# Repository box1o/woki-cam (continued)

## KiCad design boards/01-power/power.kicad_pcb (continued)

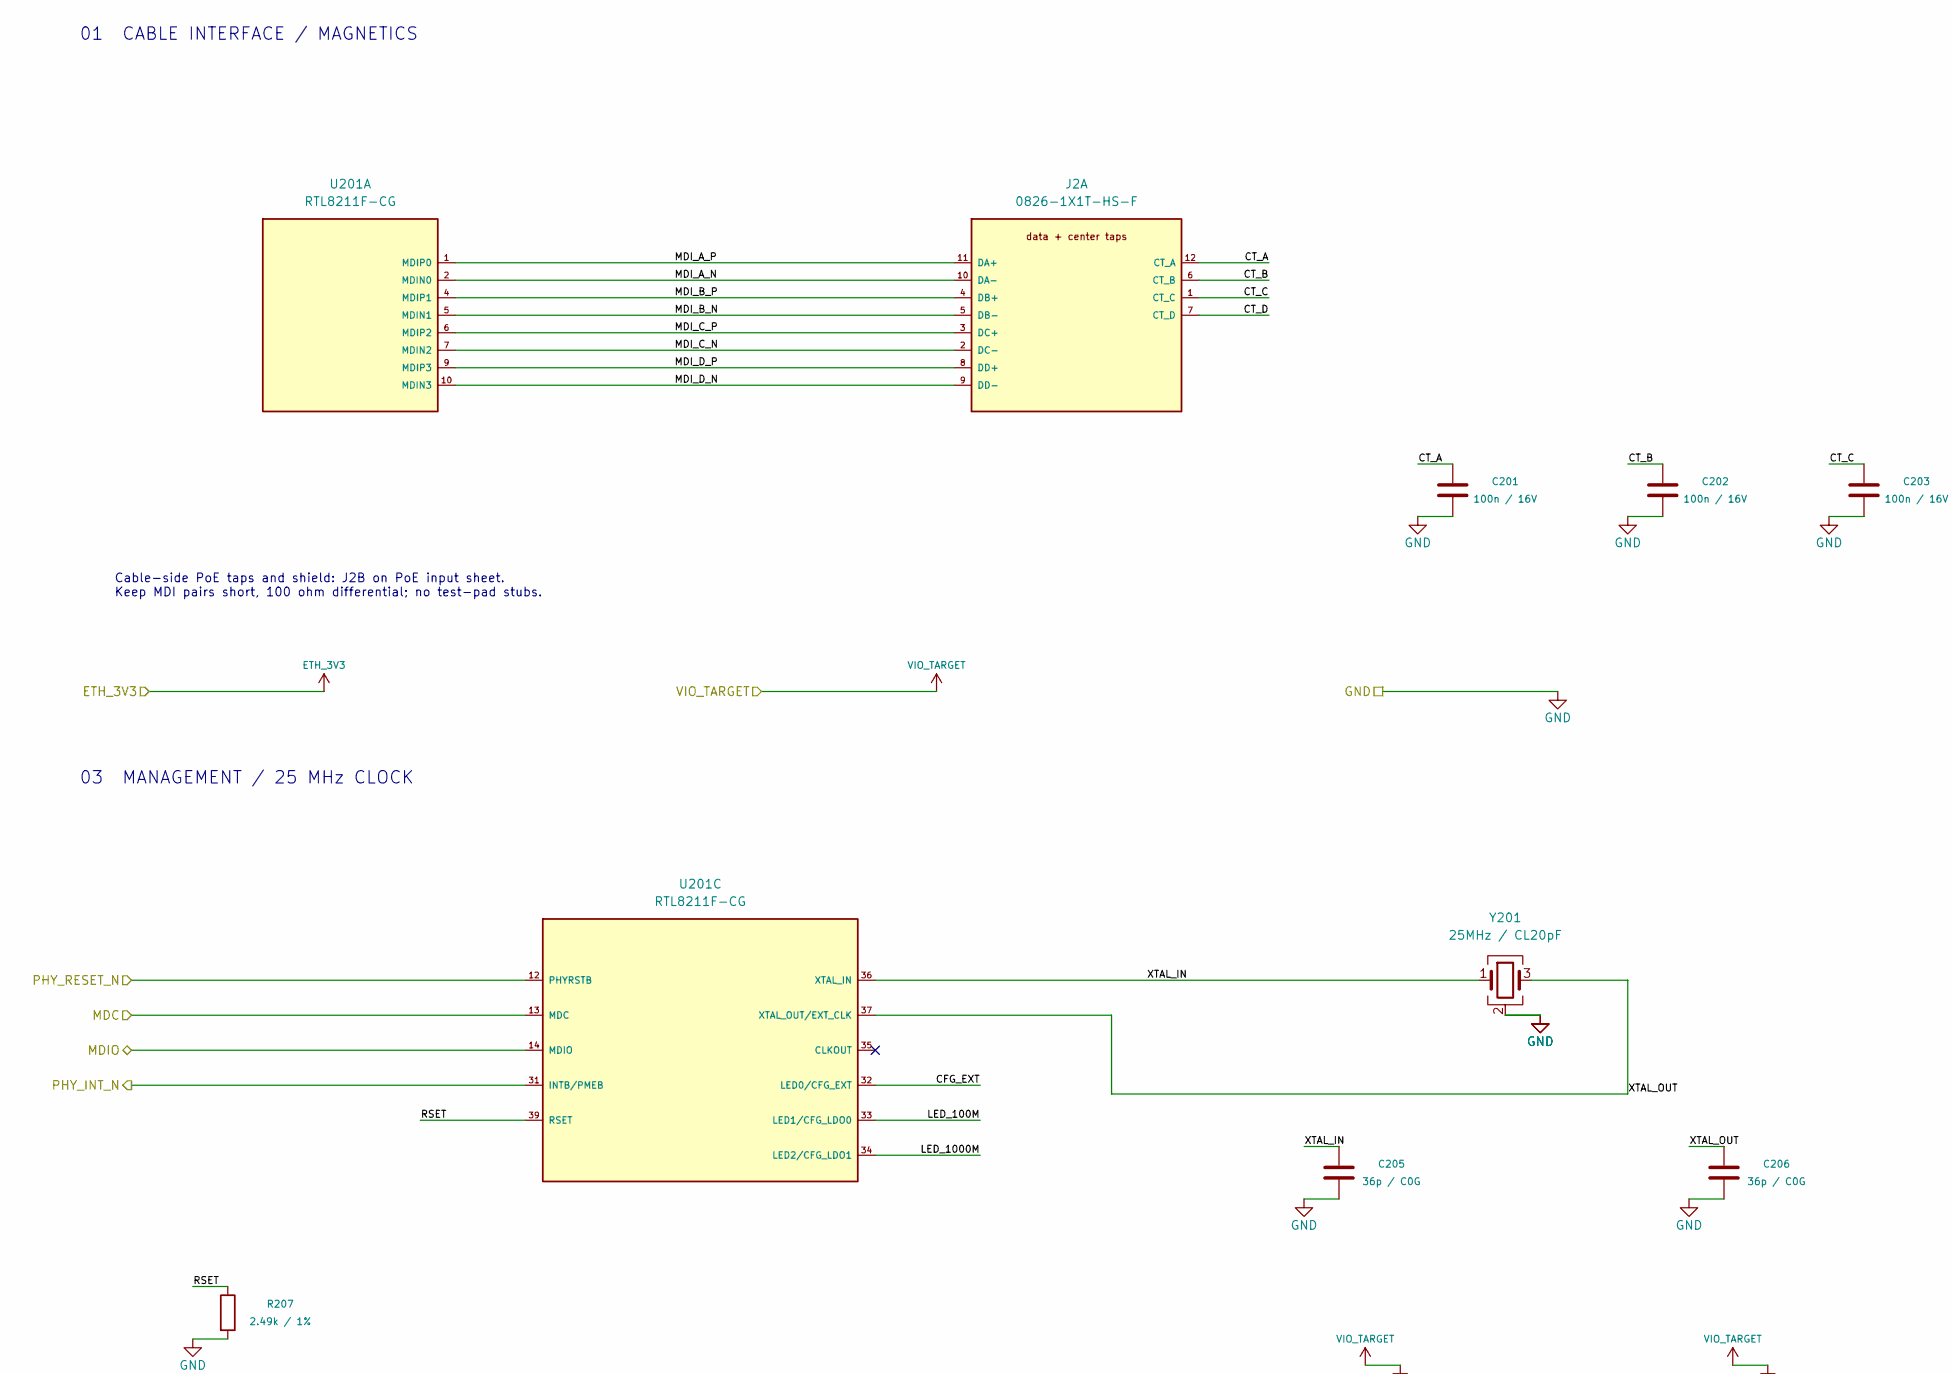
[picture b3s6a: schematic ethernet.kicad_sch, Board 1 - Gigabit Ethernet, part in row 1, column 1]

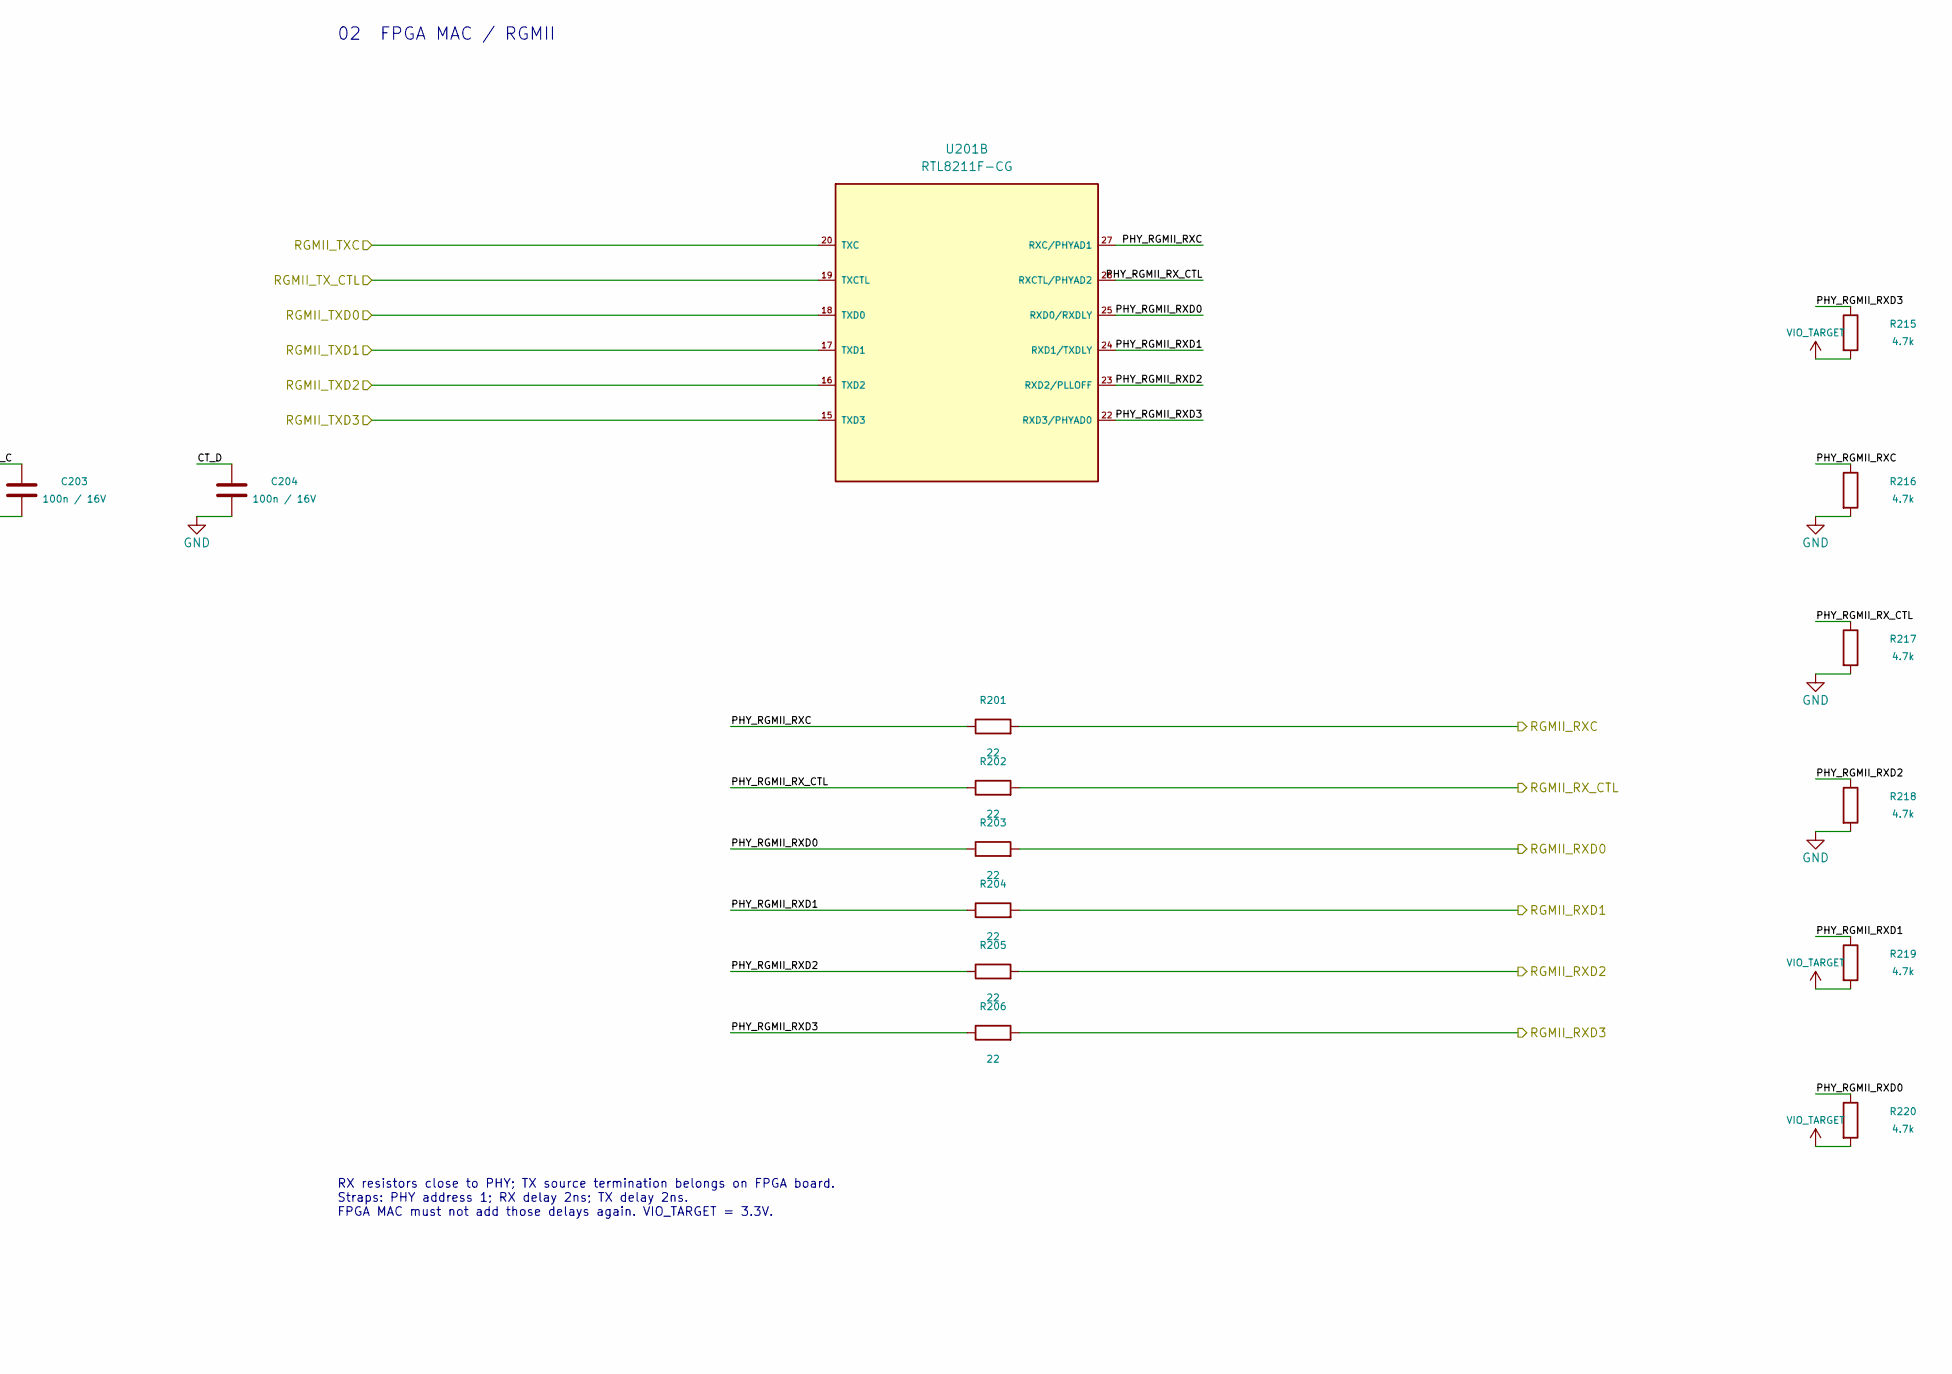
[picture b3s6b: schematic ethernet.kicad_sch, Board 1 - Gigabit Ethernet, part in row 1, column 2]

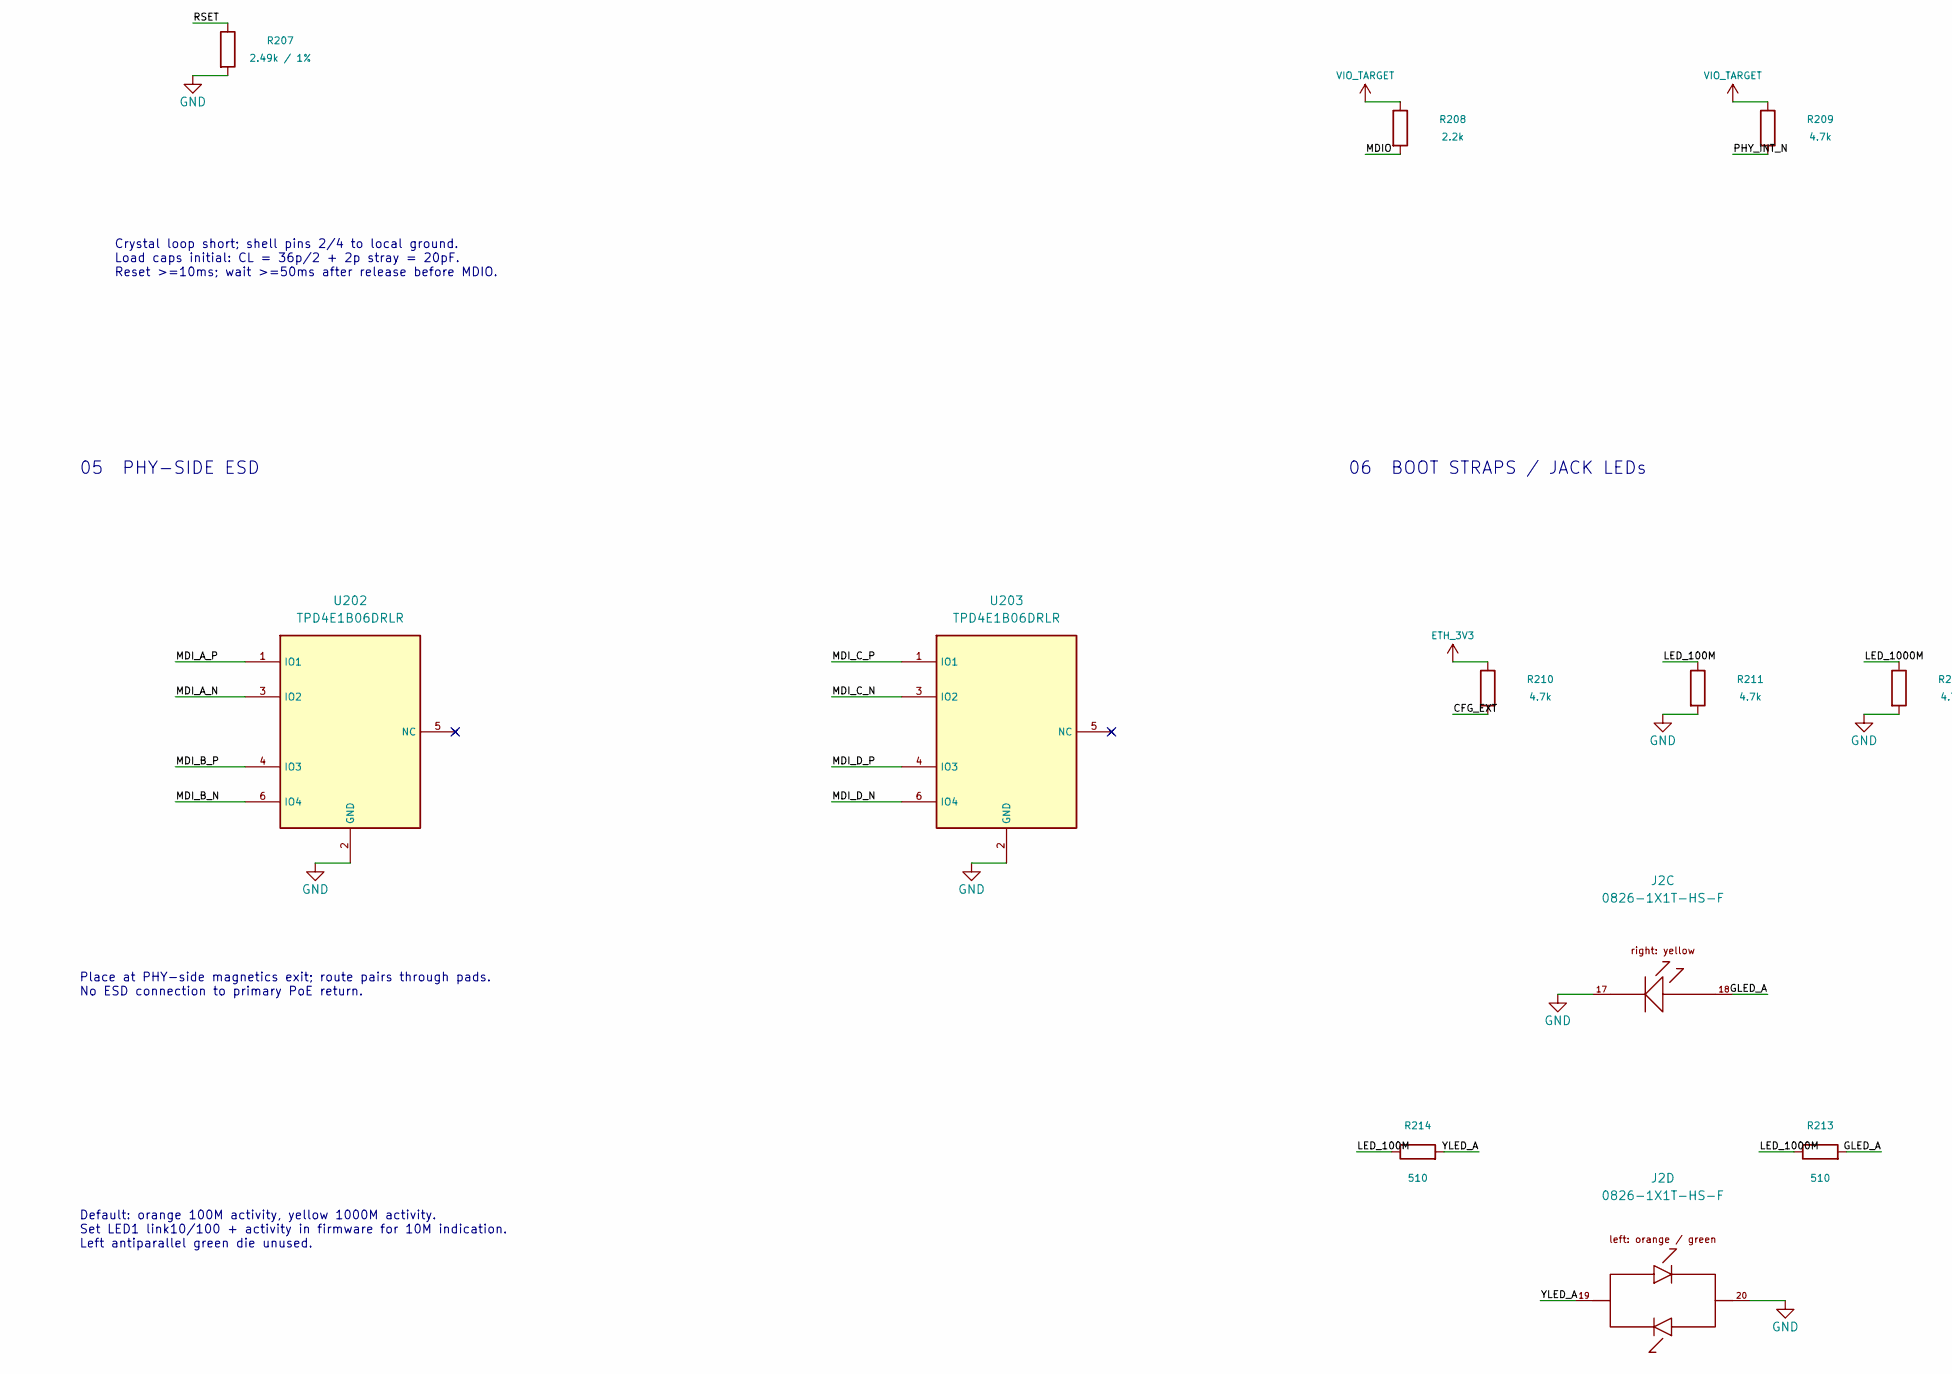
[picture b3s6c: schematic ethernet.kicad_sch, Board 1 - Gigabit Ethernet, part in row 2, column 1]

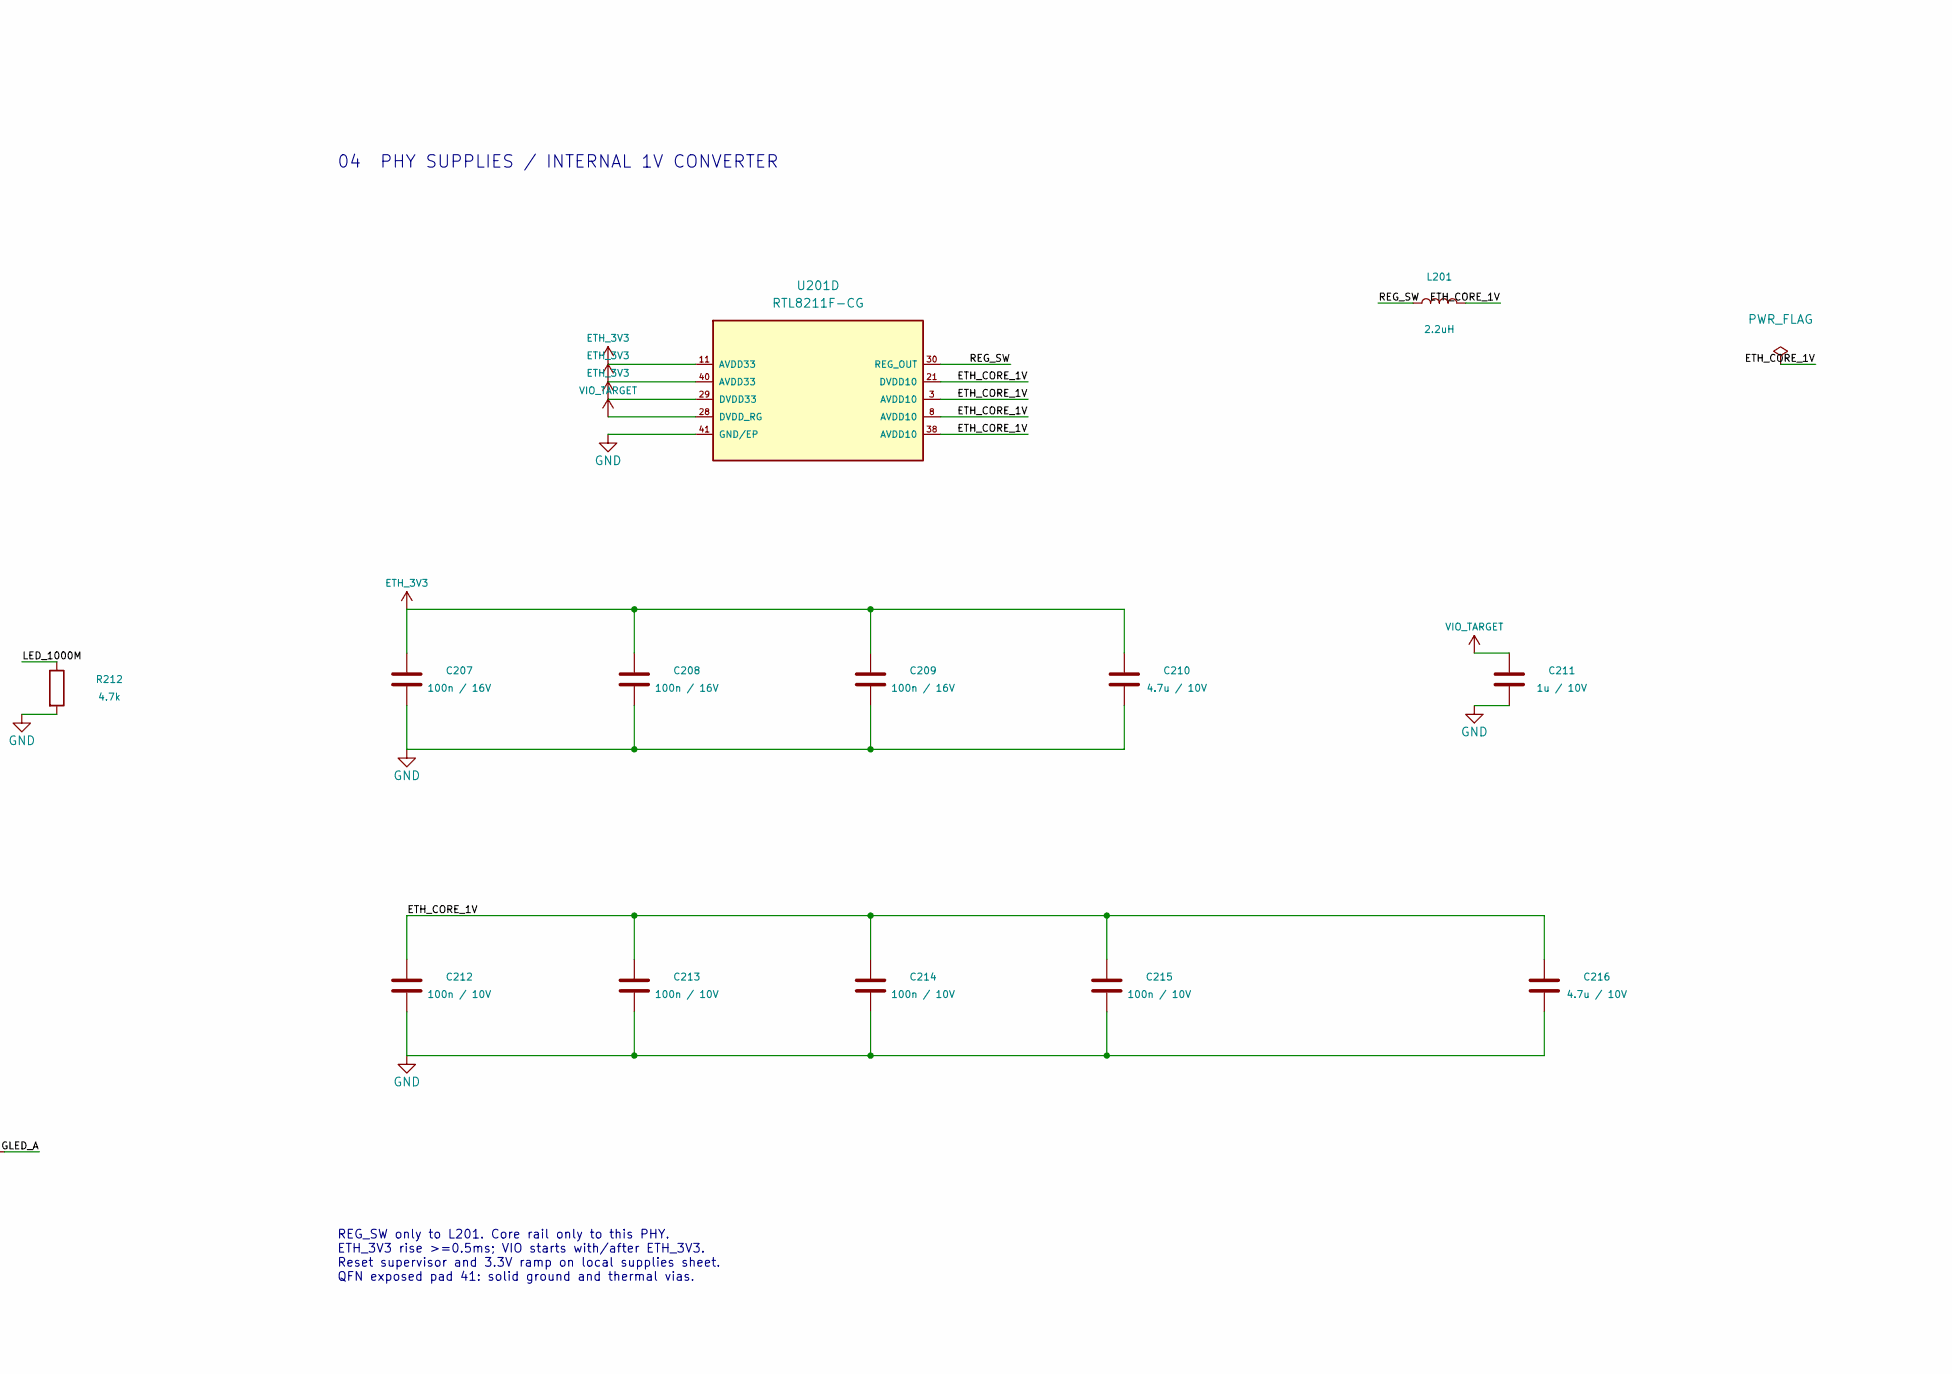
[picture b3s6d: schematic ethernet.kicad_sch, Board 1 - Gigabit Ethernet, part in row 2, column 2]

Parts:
C201, C202, C203, C204, C207, C208, C209: 100n / 16V; C_0603_1608Metric
C205, C206: 36p / C0G; C_0603_1608Metric
C210, C216: 4.7u / 10V; C_0603_1608Metric
C211: 1u / 10V; C_0603_1608Metric
C212, C213, C214, C215: 100n / 10V; C_0603_1608Metric
J2: 0826-1X1T-HS-F; 0826-1x1t-hs-f
L201: 2.2uH; lps4018; MPN LPS4018-222MR
R201, R202, R203, R204, R205, R206: 22; R_0603_1608Metric
R207: 2.49k / 1%; R_0603_1608Metric
R208: 2.2k; R_0603_1608Metric
R209, R210, R211, R212, R215, R216, R217, R218, R219, R220: 4.7k; R_0603_1608Metric
R213, R214: 510; R_0603_1608Metric
U201: RTL8211F-CG; rtl8211f-cg
U202, U203: TPD4E1B06DRLR; SOT-563
Y201: 25MHz / CL20pF; Crystal_SMD_3225-4Pin_3.2x2.5mm; MPN X322525MSB4SI

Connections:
/Gigabit Ethernet/CFG_EXT: R210.2, U201.32 (LED0/CFG_EXT)
/Gigabit Ethernet/CT_A: C201.1, J2.12 (CT_A)
/Gigabit Ethernet/CT_B: C202.1, J2.6 (CT_B)
/Gigabit Ethernet/CT_C: C203.1, J2.1 (CT_C)
/Gigabit Ethernet/CT_D: C204.1, J2.7 (CT_D)
/Gigabit Ethernet/ETH_CORE_1V: C212.1, C213.1, C214.1, C215.1, C216.1, L201.2, U201.3 (AVDD10), U201.8 (AVDD10), U201.21 (DVDD10), U201.38 (AVDD10)
/Gigabit Ethernet/GLED_A: J2.18, R213.2
/Gigabit Ethernet/LED_100M: R211.1, R214.1, U201.33 (LED1/CFG_LDO0)
/Gigabit Ethernet/LED_1000M: R212.1, R213.1, U201.34 (LED2/CFG_LDO1)
/Gigabit Ethernet/MDI_A_N: J2.10 (DA-), U201.2 (MDIN0), U202.3 (IO2)
/Gigabit Ethernet/MDI_A_P: J2.11 (DA+), U201.1 (MDIP0), U202.1 (IO1)
/Gigabit Ethernet/MDI_B_N: J2.5 (DB-), U201.5 (MDIN1), U202.6 (IO4)
/Gigabit Ethernet/MDI_B_P: J2.4 (DB+), U201.4 (MDIP1), U202.4 (IO3)
/Gigabit Ethernet/MDI_C_N: J2.2 (DC-), U201.7 (MDIN2), U203.3 (IO2)
/Gigabit Ethernet/MDI_C_P: J2.3 (DC+), U201.6 (MDIP2), U203.1 (IO1)
/Gigabit Ethernet/MDI_D_N: J2.9 (DD-), U201.10 (MDIN3), U203.6 (IO4)
/Gigabit Ethernet/MDI_D_P: J2.8 (DD+), U201.9 (MDIP3), U203.4 (IO3)
/Gigabit Ethernet/PHY_RGMII_RXC: R201.1, R216.1, U201.27 (RXC/PHYAD1)
/Gigabit Ethernet/PHY_RGMII_RXD0: R203.1, R220.1, U201.25 (RXD0/RXDLY)
/Gigabit Ethernet/PHY_RGMII_RXD1: R204.1, R219.1, U201.24 (RXD1/TXDLY)
/Gigabit Ethernet/PHY_RGMII_RXD2: R205.1, R218.1, U201.23 (RXD2/PLLOFF)
/Gigabit Ethernet/PHY_RGMII_RXD3: R206.1, R215.1, U201.22 (RXD3/PHYAD0)
/Gigabit Ethernet/PHY_RGMII_RX_CTL: R202.1, R217.1, U201.26 (RXCTL/PHYAD2)
/Gigabit Ethernet/REG_SW: L201.1, U201.30 (REG_OUT)
/Gigabit Ethernet/RSET: R207.1, U201.39 (RSET)
/Gigabit Ethernet/XTAL_IN: C205.1, U201.36 (XTAL_IN), Y201.1
/Gigabit Ethernet/XTAL_OUT: C206.1, U201.37 (XTAL_OUT/EXT_CLK), Y201.3
/Gigabit Ethernet/YLED_A: J2.19, R214.2
/MDC: U201.13 (MDC); also elsewhere on the board
/MDIO: R208.2, U201.14 (MDIO); also elsewhere on the board
/PHY_INT_N: R209.2, U201.31 (INTB/PMEB); also elsewhere on the board
/PHY_RESET_N: U201.12 (PHYRSTB); also elsewhere on the board
/RGMII_RXC: R201.2; also elsewhere on the board
/RGMII_RXD0: R203.2; also elsewhere on the board
/RGMII_RXD1: R204.2; also elsewhere on the board
/RGMII_RXD2: R205.2; also elsewhere on the board
/RGMII_RXD3: R206.2; also elsewhere on the board
/RGMII_RX_CTL: R202.2; also elsewhere on the board
/RGMII_TXC: U201.20 (TXC); also elsewhere on the board
/RGMII_TXD0: U201.18 (TXD0); also elsewhere on the board
/RGMII_TXD1: U201.17 (TXD1); also elsewhere on the board
/RGMII_TXD2: U201.16 (TXD2); also elsewhere on the board
/RGMII_TXD3: U201.15 (TXD3); also elsewhere on the board
/RGMII_TX_CTL: U201.19 (TXCTL); also elsewhere on the board
ETH_3V3: C207.1, C208.1, C209.1, C210.1, R210.1, U201.11 (AVDD33), U201.29 (DVDD33), U201.40 (AVDD33); also elsewhere on the board
VIO_TARGET: C211.1, R208.1, R209.1, R215.2, R219.2, R220.2, U201.28 (DVDD_RG); also elsewhere on the board

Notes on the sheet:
05 PHY-SIDE ESD
RX resistors close to PHY; TX source termination belongs on FPGA board. Straps: PHY address 1; RX delay 2ns; TX delay 2ns. FPGA MAC must not add those delays again. VIO_TARGET = 3.3V.
02 FPGA MAC / RGMII
Crystal loop short; shell pins 2/4 to local ground. Load caps initial: CL = 36p/2 + 2p stray = 20pF. Reset >=10ms; wait >=50ms after release before MDIO.
Cable-side PoE taps and shield: J2B on PoE input sheet. Keep MDI pairs short, 100 ohm differential; no test-pad stubs.
03 MANAGEMENT / 25 MHz CLOCK
01 CABLE INTERFACE / MAGNETICS
Default: orange 100M activity, yellow 1000M activity. Set LED1 link10/100 + activity in firmware for 10M indication. Left antiparallel green die unused.
Place at PHY-side magnetics exit; route pairs through pads. No ESD connection to primary PoE return.
06 BOOT STRAPS / JACK LEDs
04 PHY SUPPLIES / INTERNAL 1V CONVERTER
REG_SW only to L201. Core rail only to this PHY. ETH_3V3 rise >=0.5ms; VIO starts with/after ETH_3V3. Reset supervisor and 3.3V ramp on local supplies sheet. QFN exposed pad 41: solid ground and thermal vias.

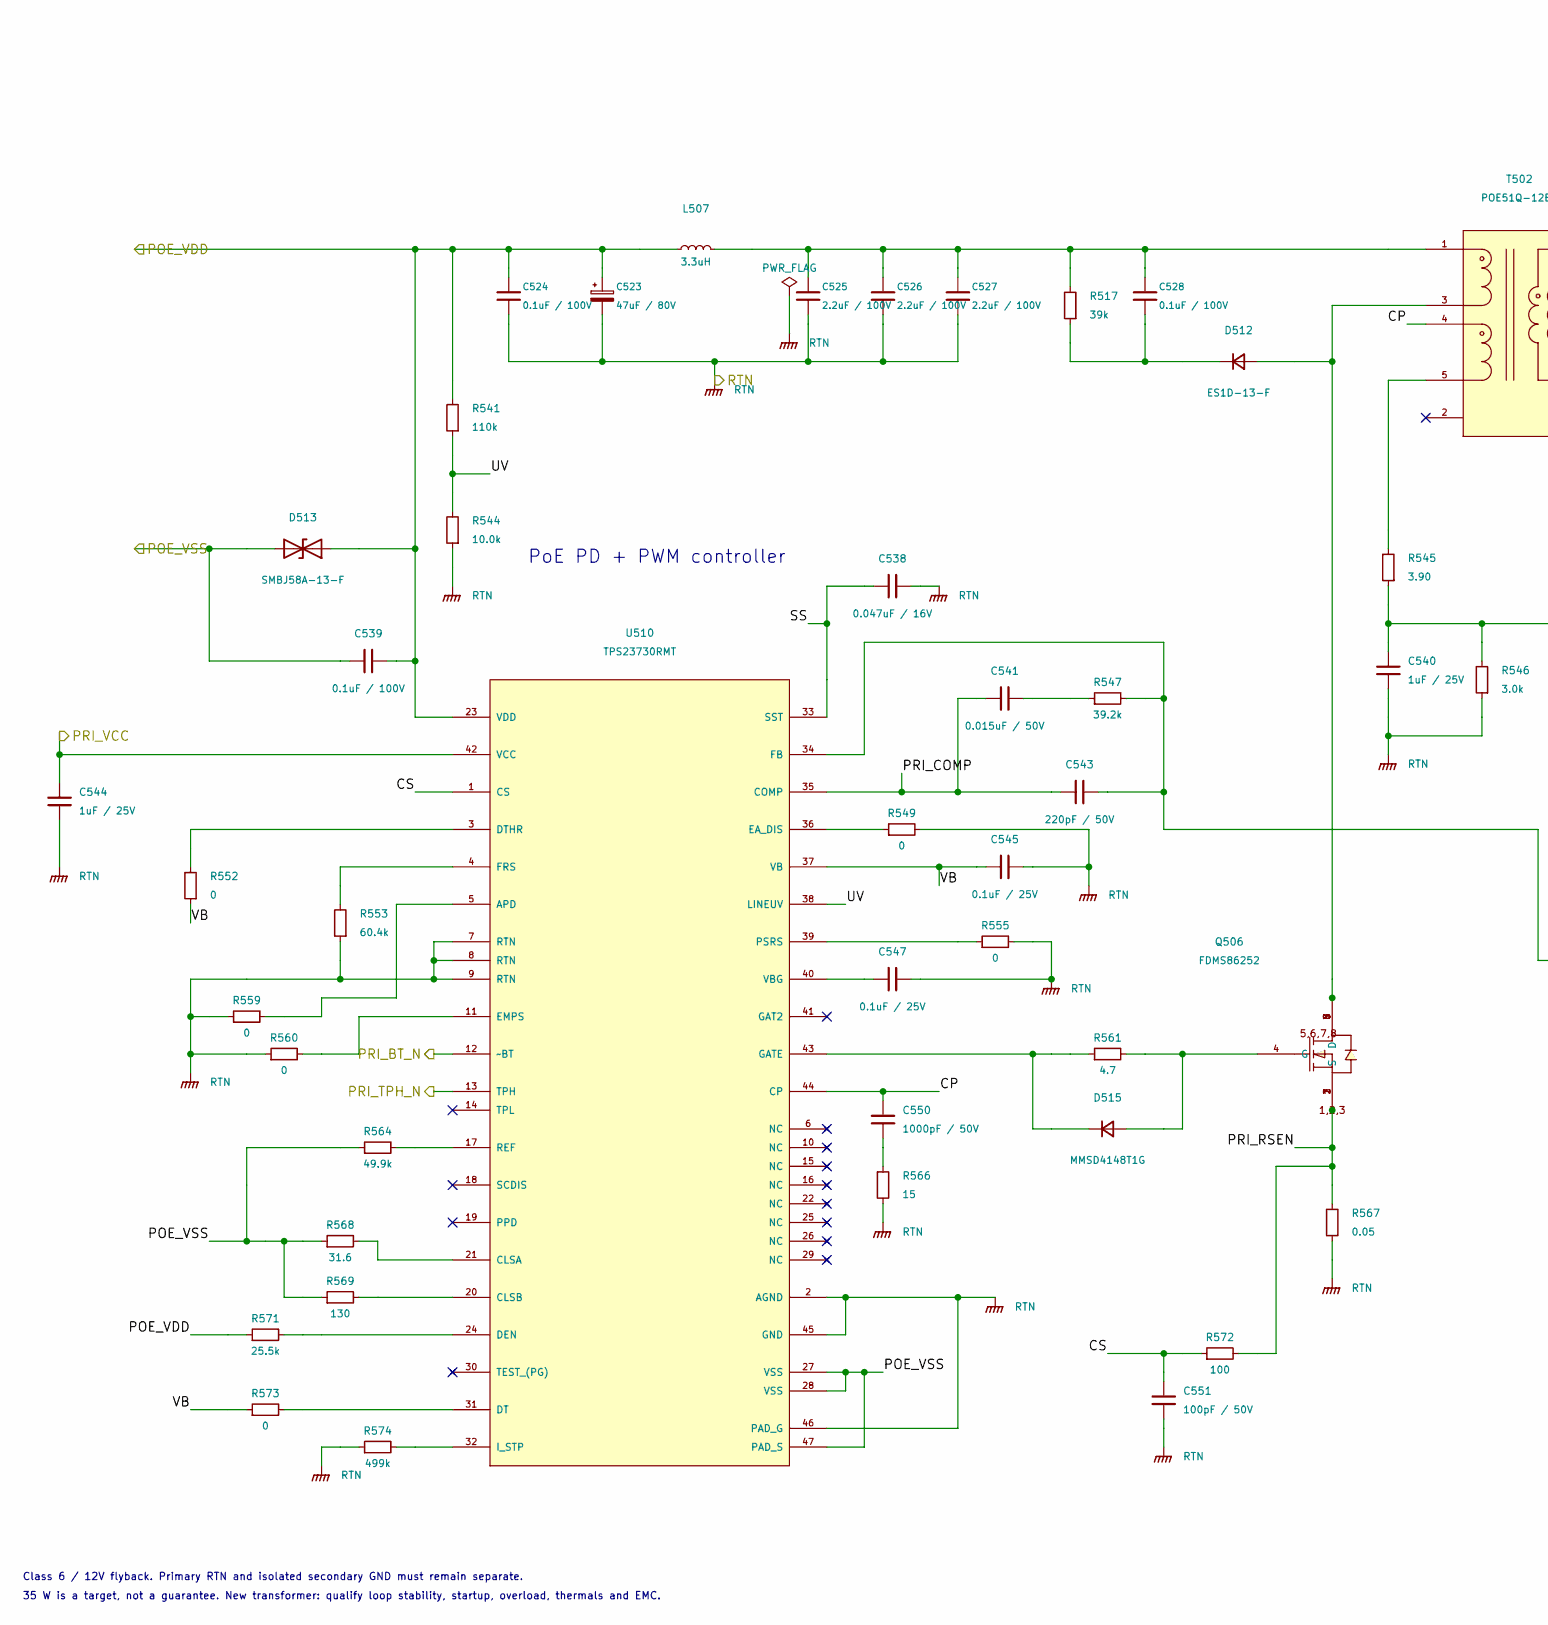
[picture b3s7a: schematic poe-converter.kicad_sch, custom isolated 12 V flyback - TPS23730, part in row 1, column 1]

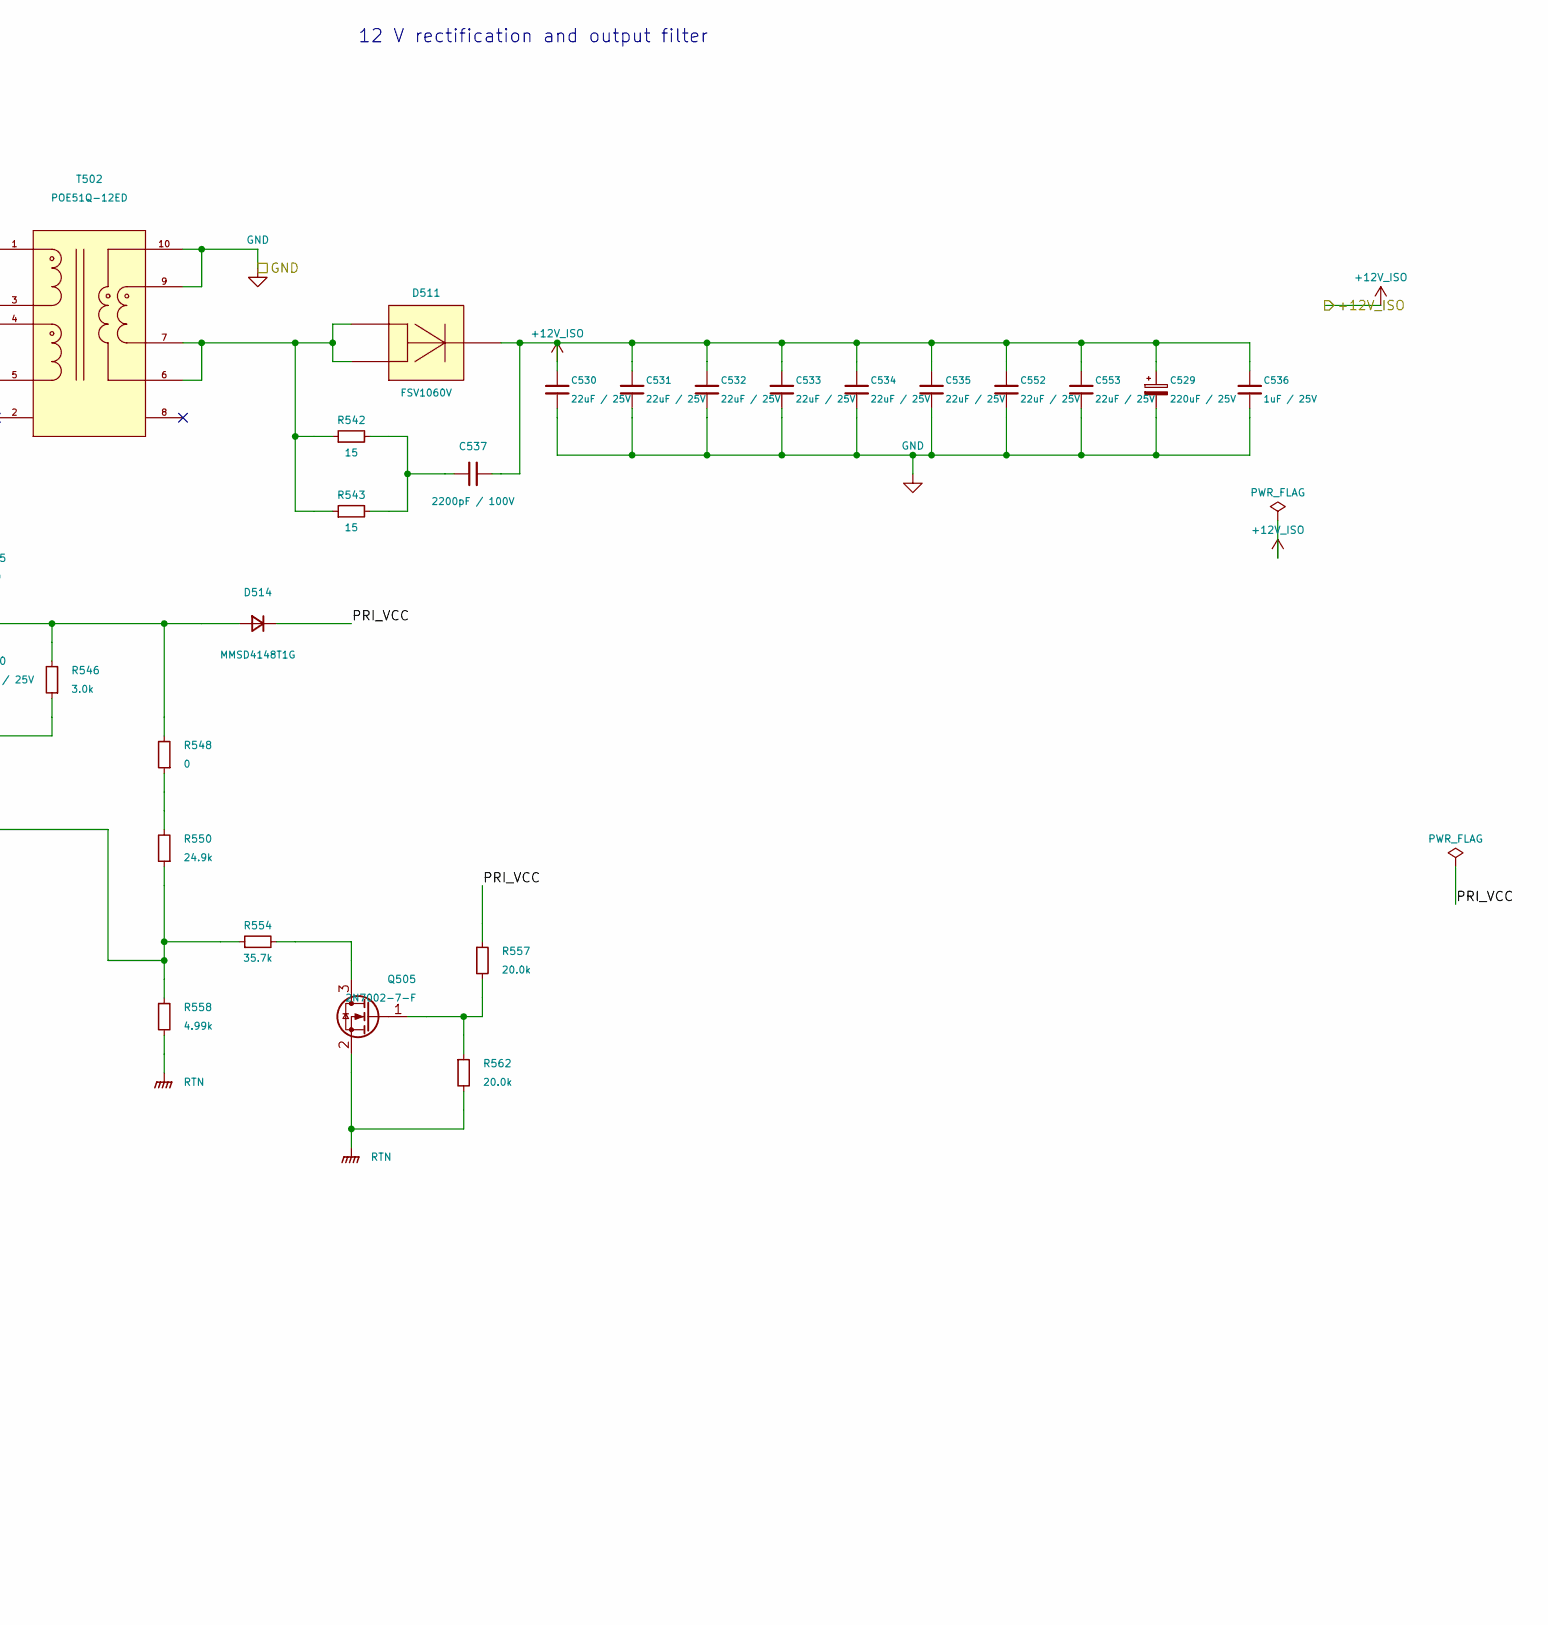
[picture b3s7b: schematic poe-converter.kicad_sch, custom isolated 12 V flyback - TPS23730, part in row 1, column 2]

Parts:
C523: 47uF / 80V; panasonic_fk_g_10x10.2
C524, C528, C539: 0.1uF / 100V; C_0805_2012Metric
C525, C526, C527: 2.2uF / 100V; C_1210_3225Metric
C529: 220uF / 25V; panasonic_fk_f_8x10.2
C530, C531, C532, C533, C534, C535, C552, C553: 22uF / 25V; C_1210_3225Metric
C536, C540, C544: 1uF / 25V; C_0603_1608Metric
C537: 2200pF / 100V; C_0603_1608Metric
C538: 0.047uF / 16V; C_0603_1608Metric
C541: 0.015uF / 50V; C_0603_1608Metric
C543: 220pF / 50V; C_0603_1608Metric
C545, C547: 0.1uF / 25V; C_0603_1608Metric
C550: 1000pF / 50V; C_0603_1608Metric
C551: 100pF / 50V; C_0603_1608Metric
D511: FSV1060V; TO-277A
D512: ES1D-13-F; D_SMA
D513: SMBJ58A-13-F; D_SMB
D514, D515: MMSD4148T1G; D_SOD-123
L507: 3.3uH; lps4018-332mlb
Q505: 2N7002-7-F; SOT-23
Q506: FDMS86252; fdms86252
R517: 39k; R_1206_3216Metric
R541: 110k; R_0603_1608Metric
R542, R543: 15; R_2512_6332Metric
R544: 10.0k; R_0603_1608Metric
R545: 3.90; R_0805_2012Metric
R546: 3.0k; R_1206_3216Metric
R547: 39.2k; R_0603_1608Metric
R548, R549, R552, R555, R559, R560, R573: 0; R_0603_1608Metric
R550: 24.9k; R_0603_1608Metric
R553: 60.4k; R_0603_1608Metric
R554: 35.7k; R_0603_1608Metric
R557, R562: 20.0k; R_0603_1608Metric
R558: 4.99k; R_0603_1608Metric
R561: 4.7; R_0603_1608Metric
R564: 49.9k; R_0603_1608Metric
R566: 15; R_1206_3216Metric
R567: 0.05; R_2010_5025Metric
R568: 31.6; R_0805_2012Metric
R569: 130; R_0805_2012Metric
R571: 25.5k; R_0603_1608Metric
R572: 100; R_0603_1608Metric
R574: 499k; R_0603_1608Metric
T502: POE51Q-12ED; poe51q-12ed
U510: TPS23730RMT; tps23730rmt

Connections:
+12V_ISO: C529.1, C530.2, C531.2, C532.2, C533.2, C534.2, C535.2, C536.1, C537.1, C552.2, C553.2, D511.3; also elsewhere on the board
/POE_VDD: C523.1, C524.1, C539.1, D513.1 (A1), L507.1, R541.2, R571.1, U510.23 (VDD); also elsewhere on the board
/POE_VSS: C539.2, D513.2 (A2), R564.1, R568.1, R569.1, U510.27 (VSS), U510.28 (VSS), U510.47 (PAD_S); also elsewhere on the board
/PRI_BT_N: U510.12 (~BT); also elsewhere on the board
/PRI_TPH_N: U510.13 (TPH); also elsewhere on the board
/PRI_VCC: C544.1, D514.1 (K), R557.1, U510.42 (VCC); also elsewhere on the board
/custom isolated 12V converter/CP: C550.1, T502.4, U510.44 (CP)
/custom isolated 12V converter/CS: C551.2, R572.1, U510.1 (CS)
/custom isolated 12V converter/PRI_COMP: C541.2, C543.2, U510.35 (COMP)
/custom isolated 12V converter/PRI_RSEN: Q506.1 (S), Q506.2 (S), Q506.3 (S), R567.1, R572.2
/custom isolated 12V converter/SS: C538.1, U510.33 (SST)
/custom isolated 12V converter/UV: R541.1, R544.2, U510.38 (LINEUV)
/custom isolated 12V converter/VB: C545.1, R552.1, R573.1, U510.37 (VB)
unnamed: C525.1, C526.1, C527.1, C528.2, L507.2, R517.2, T502.1
unnamed: C537.2, R542.2, R543.2
unnamed: C541.1, R547.1
unnamed: C550.2, R566.1
unnamed: D511.1, D511.2, R542.1, R543.1, T502.6, T502.7
unnamed: D512.2 (A), Q506.5 (D), Q506.6 (D), Q506.7 (D), Q506.8 (D), T502.3
unnamed: C528.1, D512.1 (K), R517.1
unnamed: C540.1, D514.2 (A), R545.1, R546.2, R548.2
unnamed: D515.2 (A), Q506.4 (G), R561.2
unnamed: D515.1 (K), R561.1, U510.43 (GATE)
unnamed: Q505.3 (D), R554.2
unnamed: Q505.1 (G), R557.2, R562.1
unnamed: R545.2, T502.5
unnamed: R548.1, R550.2
unnamed: R559.2, U510.5 (APD)
unnamed: R568.2, U510.21 (CLSA)
unnamed: R569.2, U510.20 (CLSB)
unnamed: R571.2, U510.24 (DEN)
unnamed: R573.2, U510.31 (DT)
unnamed: R552.2, U510.3 (DTHR)
unnamed: R549.1, U510.36 (EA_DIS)
unnamed: R560.2, U510.11 (EMPS)
unnamed: C543.1, R547.2, R550.1, R554.1, R558.1, U510.34 (FB)
unnamed: R553.2, U510.4 (FRS)
unnamed: R574.2, U510.32 (I_STP)
unnamed: R555.1, U510.39 (PSRS)
unnamed: R564.2, U510.17 (REF)
unnamed: C547.2, U510.40 (VBG)
RTN: C523.2, C524.2, C525.2, C526.2, C527.2, C538.2, C540.2, C544.2, C545.2, C547.1, C551.1, Q505.2 (S), R544.1, R546.1, R549.2, R553.1, R555.2, R558.2, R559.1, R560.1, R562.2, R566.2, R567.2, R574.1, U510.2 (AGND), U510.7 (RTN), U510.8 (RTN), U510.9 (RTN), U510.45 (GND), U510.46 (PAD_G)

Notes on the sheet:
Class 6 / 12V flyback. Primary RTN and isolated secondary GND must remain separate.
PoE PD + PWM controller
12 V rectification and output filter
35 W is a target, not a guarantee. New transformer: qualify loop stability, startup, overload, thermals and EMC.

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
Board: 8 copper layers, 232 parts (0 on the bottom side), 150 nets, no tracks yet.

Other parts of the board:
H1, H2, H3, H4: M3 / CHASSIS; mounting-hole-m3

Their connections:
CHASSIS: H1.1, H2.1, H3.1, H4.1; also elsewhere on the board
